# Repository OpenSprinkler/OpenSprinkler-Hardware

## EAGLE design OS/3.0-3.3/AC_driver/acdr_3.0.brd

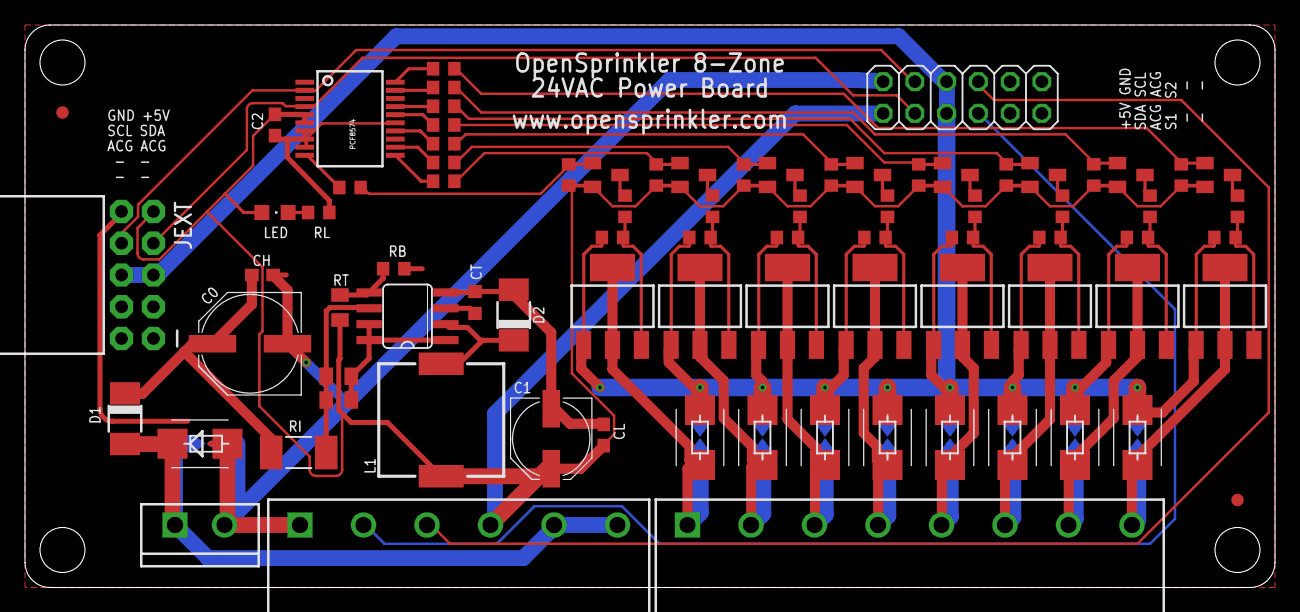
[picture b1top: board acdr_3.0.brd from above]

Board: 2 copper layers, 100.0 x 45.0 mm, 91 parts (0 on the bottom side), 55 nets.

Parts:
C0: 100uF; PANASONIC_E
C1: 100uF; PANASONIC_D
C2: 0.1u; C0603
CH: 0.1u; C0603
CL: 0.1u; C0603
CT: 150pF; C0603K
D1: M7; DO-214AC
D2: SS14; DO-214AC
JCOM: SCREWTERMINAL-5MM-6
JCON: 2X06
JEXT: M05X2RAF; 2X5-RAF
JPWR: SCREWTERMINAL-4MM-2-X
L1: 220uH; SRU1038
LED: CHIPLED_0805
MC3063: 34063; SO08
PCF8574: PCF8574; SSOP20
Q1, Q2, Q3, Q4, Q5, Q6, Q7, Q8: BSS84; SOT23
RB: 1.6K; R0603
RB1, RB2, RB3, RB4, RB5, RB6, RB7, RB8: 470K; R0603
RI: 3.3; R2010
RL: 1K; R0603
RQ1, RQ2, RQ3, RQ4, RQ5, RQ6, RQ7, RQ8: 10K; R0603
RSC, RSC1: 1; R0805
RT: 4.7K; R0805
RT1, RT2, RT3, RT4, RT5, RT6, RT7, RT8: 220; R0603
RU1, RU2, RU3, RU4, RU5, RU6, RU7, RU8: 470K; R0603
S02: SCREWTERMINAL-5MM-8
SP0, SP1, SP2, SP3, SP4, SP5, SP6, SP7, SP8: PCB-SGAP
T1: BT1308W; SOT223
T2, T3, T4, T5, T6, T7, T8: SOT223
TVS0: 43CA; SMB
TVS1: SMBJ48CA; SMB
TVS2, TVS3, TVS4, TVS5, TVS6, TVS7, TVS8: TVSSMB; SMB
U$1, U$2: FIDUCIAL; FIDUCIAL_1MM

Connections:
ACRET: JCON.5, JCON.6, JEXT.5, JEXT.6, RB1.1, RB2.1, RB3.1, RB4.1, RB5.1, RB6.1, RB7.1, RB8.1, SP1.1, SP2.1, SP3.1, SP4.1, SP5.1, SP6.1, SP7.1, SP8.1, T1.1, T2.1, T3.1, T4.1, T5.1, T6.1, T7.1, T8.1, TVS1.C, TVS2.C, TVS3.C, TVS4.C, TVS5.C, TVS6.C, TVS7.C, TVS8.C
COM: D1.A, JCOM.5, JCOM.6, JPWR.1, SP0.1, TVS0.C
GND: C0.-, C1.-, C2.2, CH.2, CL.2, CT.2, D2.A, JCOM.1, JCON.2, JEXT.10, JPWR.2, MC3063.4, PCF8574.7, PCF8574.8, PCF8574.9, PCF8574.15, RB.2, RL.2, SP0.2, TVS0.A
unnamed: MC3063.1, MC3063.7, MC3063.8, RSC.1, RSC1.1
unnamed: Q1.3, RT1.2
unnamed: Q2.3, RT2.2
unnamed: Q3.3, RT3.2
unnamed: Q4.3, RT4.2
unnamed: Q5.3, RT5.2
unnamed: Q6.3, RT6.2
unnamed: RB1.2, RT1.1, T1.3
unnamed: RB2.2, RT2.1, T2.3
unnamed: Q7.3, RT7.2
unnamed: Q8.3, RT8.2
unnamed: Q1.1, RQ1.1, RU1.2
unnamed: Q2.1, RQ2.1, RU2.2
unnamed: Q3.1, RQ3.1, RU3.2
unnamed: RB3.2, RT3.1, T3.3
unnamed: RB4.2, RT4.1, T4.3
unnamed: D2.C, L1.1, MC3063.2
unnamed: RB5.2, RT5.1, T5.3
unnamed: RB6.2, RT6.1, T6.3
unnamed: Q4.1, RQ4.1, RU4.2
unnamed: RB7.2, RT7.1, T7.3
unnamed: RB8.2, RT8.1, T8.3
unnamed: Q5.1, RQ5.1, RU5.2
unnamed: CT.1, MC3063.3
unnamed: Q6.1, RQ6.1, RU6.2
unnamed: MC3063.5, RB.1, RT.2
unnamed: MC3063.6, RI.2, RSC.2, RSC1.2
unnamed: LED.C, RL.1
unnamed: Q7.1, RQ7.1, RU7.2
unnamed: Q8.1, RQ8.1, RU8.2
unnamed: S02.1, SP1.2, T1.2, T1.4, TVS1.A
unnamed: S02.2, SP2.2, T2.2, T2.4, TVS2.A
unnamed: S02.3, SP3.2, T3.2, T3.4, TVS3.A
unnamed: S02.4, SP4.2, T4.2, T4.4, TVS4.A
unnamed: S02.5, SP5.2, T5.2, T5.4, TVS5.A
unnamed: S02.6, SP6.2, T6.2, T6.4, TVS6.A
unnamed: S02.7, SP7.2, T7.2, T7.4, TVS7.A
unnamed: S02.8, SP8.2, T8.2, T8.4, TVS8.A
P0: PCF8574.10, RQ1.2
P1: PCF8574.11, RQ2.2
P2: PCF8574.12, RQ3.2
P3: PCF8574.14, RQ4.2
P4: PCF8574.16, RQ5.2
P5: PCF8574.17, RQ6.2
P6: PCF8574.19, RQ7.2
P7: PCF8574.20, RQ8.2
RECAC: C0.+, CH.1, D1.C, RI.1
S1: JCOM.2, JCON.7
S2: JCOM.3, JCON.8
SCL: JCON.4, JEXT.8, PCF8574.2
SDA: JCON.3, JEXT.7, PCF8574.4
VIN: C1.+, C2.1, CL.1, JCOM.4, JCON.1, JEXT.9, L1.2, LED.A, PCF8574.5, PCF8574.6, Q1.2, Q2.2, Q3.2, Q4.2, Q5.2, Q6.2, Q7.2, Q8.2, RT.1, RU1.1, RU2.1, RU3.1, RU4.1, RU5.1, RU6.1, RU7.1, RU8.1

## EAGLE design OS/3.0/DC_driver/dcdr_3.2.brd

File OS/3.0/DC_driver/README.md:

- Original DC driver board 3.0 uses PCF8574 (8-channel) IO expander with PNP transistor per channel.

- DC driver 3.1 (i.e. revision 1) uses a PCA9555 (16-channel) IO expander.

- DC driver 3.2 (i.e. revision 2) matches master version 3.2 with support for wired Ethernet module.

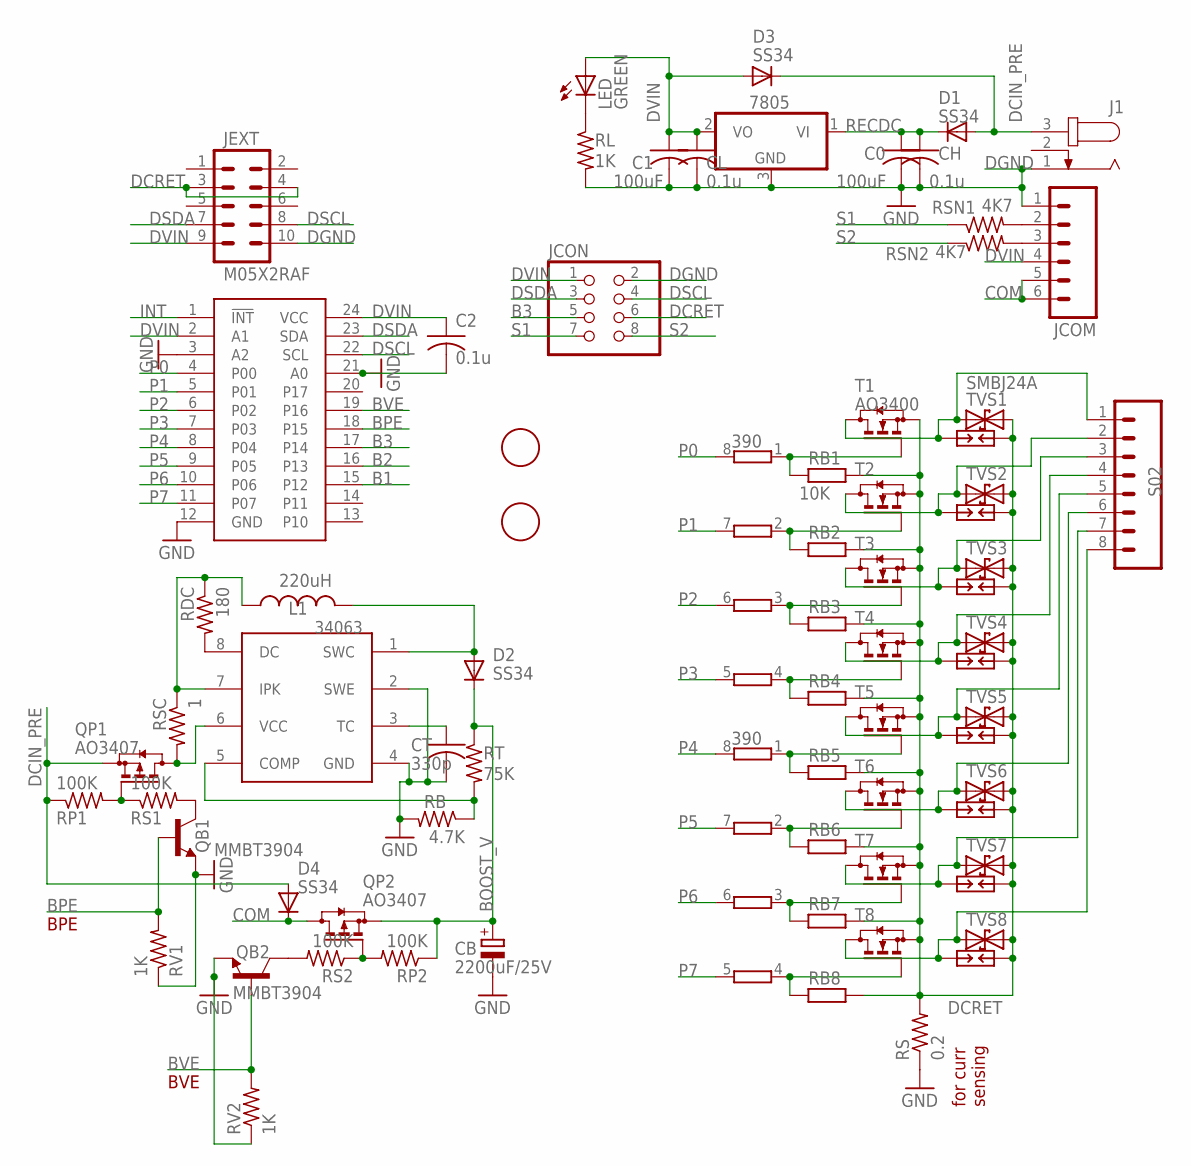
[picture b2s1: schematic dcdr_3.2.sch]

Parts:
7805: 7805DT; TO252
34063: MC34063; SO08
C0, C1: 100uF; C0805K
C2: 0.1u; C0603
CB: 2200uF/25V; E7,5-16
CH: 0.1u; C0603
CL: 0.1u; C0603
CT: 330p; C0603K
D1, D2, D3, D4: SS34; SMB
J1: JACK-PLUG0; SPC4077
JCOM: M065MM; SCREWTERMINAL-5MM-6
JCON: PINHD-2X4; 2X04
JEXT: M05X2RAF; 2X5-RAF
L1: 220uH; CR54
LED: GREEN; CHIPLED_0805
PCA9555: PCA9555; TSSOP24
QB1, QB2: MMBT3904; SOT23-3
QP1, QP2: AO3407; SOT23
RB: 4.7K; R0603
RB1, RB2, RB3, RB4, RB5, RB6, RB7, RB8: 10K; R0603
RDC: 180; R0603
RL: 1K; R0603
RN1, RN2: 390; EXB38V
RP1, RP2: 100K; R0603
RS: 0.2; R2512
RS1, RS2: 100K; R0603
RSC: 1; R0603
RSN1, RSN2: 4K7; R0603
RT: 75K; R0603
RV1, RV2: 1K; R0603
S02: M085MM-8; SCREWTERMINAL-5MM-8
SP1, SP2, SP3, SP4, SP5, SP6, SP7, SP8: PCB-SGAP
T1, T2, T3, T4, T5, T6, T7, T8: AO3400; SOT23
TVS1, TVS2, TVS3, TVS4, TVS5, TVS6, TVS7, TVS8: SMBJ24A; SMB
U$1, U$2: FIDUCIAL; FIDUCIAL_1MM

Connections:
B1: PCA9555.15 (P12)
B2: PCA9555.16 (P13)
B3: JCON.5, PCA9555.17 (P14)
BOOST_V: CB.+, D2.C, QP2.2 (S), RP2.1, RT.1
BPE: PCA9555.18 (P15), QB1.1 (B), RV1.2
BVE: PCA9555.19 (P16), QB2.1 (B), RV2.2
COM: D4.C, JCOM.5, JCOM.6, QP2.3 (D)
DCIN_PRE: D1.A, D3.C, D4.A, J1.3, QP1.2 (S), RP1.1
DCRET: JCON.6, JEXT.3, JEXT.4, RB1.1, RB2.1, RB3.1, RB4.1, RB5.1, RB6.1, RB7.1, RB8.1, RS.2, SP1.1, SP2.1, SP3.1, SP4.1, SP5.1, SP6.1, SP7.1, SP8.1, T1.2 (S), T2.2 (S), T3.2 (S), T4.2 (S), T5.2 (S), T6.2 (S), T7.2 (S), T8.2 (S), TVS1.C, TVS2.C, TVS3.C, TVS4.C, TVS5.C, TVS6.C, TVS7.C, TVS8.C
DGND: 7805.3 (GND), 34063.2 (SWE), 34063.4 (GND), C0.2, C1.2, C2.2, CB.-, CH.2, CL.2, CT.2, J1.1, JCOM.1, JCON.2, JEXT.10, PCA9555.3 (A2), PCA9555.12 (GND), PCA9555.21 (A0), QB1.2 (E), QB2.2 (E), RB.2, RL.2, RS.1, RV1.1, RV2.1
DSCL: JCON.4, JEXT.8, PCA9555.22 (SCL)
DSDA: JCON.3, JEXT.7, PCA9555.23 (SDA)
DVIN: 7805.2 (VO), C1.1, C2.1, CL.1, D3.A, JCOM.4, JCON.1, JEXT.9, LED.A, PCA9555.2 (A1), PCA9555.24 (VCC)
INT: PCA9555.1 (!INT)
unnamed: 34063.1 (SWC), D2.A, L1.P$2 (2)
unnamed: JCOM.2, RSN1.2
unnamed: JCOM.3, RSN2.2
unnamed: RB1.2, RN1.1, T1.1 (G)
unnamed: RB2.2, RN1.2 (1), T2.1 (G)
unnamed: RB3.2, RN1.3 (1), T3.1 (G)
unnamed: RB4.2, RN1.4 (1), T4.1 (G)
unnamed: 34063.3 (TC), CT.1
unnamed: RB5.2, RN2.1, T5.1 (G)
unnamed: RB6.2, RN2.2 (1), T6.1 (G)
unnamed: RB7.2, RN2.3 (1), T7.1 (G)
unnamed: RB8.2, RN2.4 (1), T8.1 (G)
unnamed: 34063.8 (DC), RDC.2
unnamed: 34063.7 (IPK), L1.P$1 (1), RDC.1, RSC.1
unnamed: 34063.6 (VCC), QP1.3 (D), RSC.2
unnamed: LED.C, RL.1
unnamed: 34063.5 (COMP), RB.1, RT.2
unnamed: QP1.1 (G), RP1.2, RS1.1
unnamed: QB2.3 (C), RS2.2
unnamed: QB1.3 (C), RS1.2
unnamed: QP2.1 (G), RP2.2, RS2.1
unnamed: S02.1, SP1.2, T1.3 (D), TVS1.A
unnamed: S02.2, SP2.2, T2.3 (D), TVS2.A
unnamed: S02.3, SP3.2, T3.3 (D), TVS3.A
unnamed: S02.4, SP4.2, T4.3 (D), TVS4.A
unnamed: S02.5, SP5.2, T5.3 (D), TVS5.A
unnamed: S02.6, SP6.2, T6.3 (D), TVS6.A
unnamed: S02.7, SP7.2, T7.3 (D), TVS7.A
unnamed: S02.8, SP8.2, T8.3 (D), TVS8.A
P0: PCA9555.4 (P00), RN1.8 (2)
P1: PCA9555.5 (P01), RN1.7 (2)
P2: PCA9555.6 (P02), RN1.6 (2)
P3: PCA9555.7 (P03), RN1.5 (2)
P4: PCA9555.8 (P04), RN2.8 (2)
P5: PCA9555.9 (P05), RN2.7 (2)
P6: PCA9555.10 (P06), RN2.6 (2)
P7: PCA9555.11 (P07), RN2.5 (2)
RECDC: 7805.1 (VI), C0.1, CH.1, D1.C
S1: JCON.7, RSN1.1
S2: JCON.8, RSN2.1

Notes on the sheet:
BPE
BVE
for curr sensing

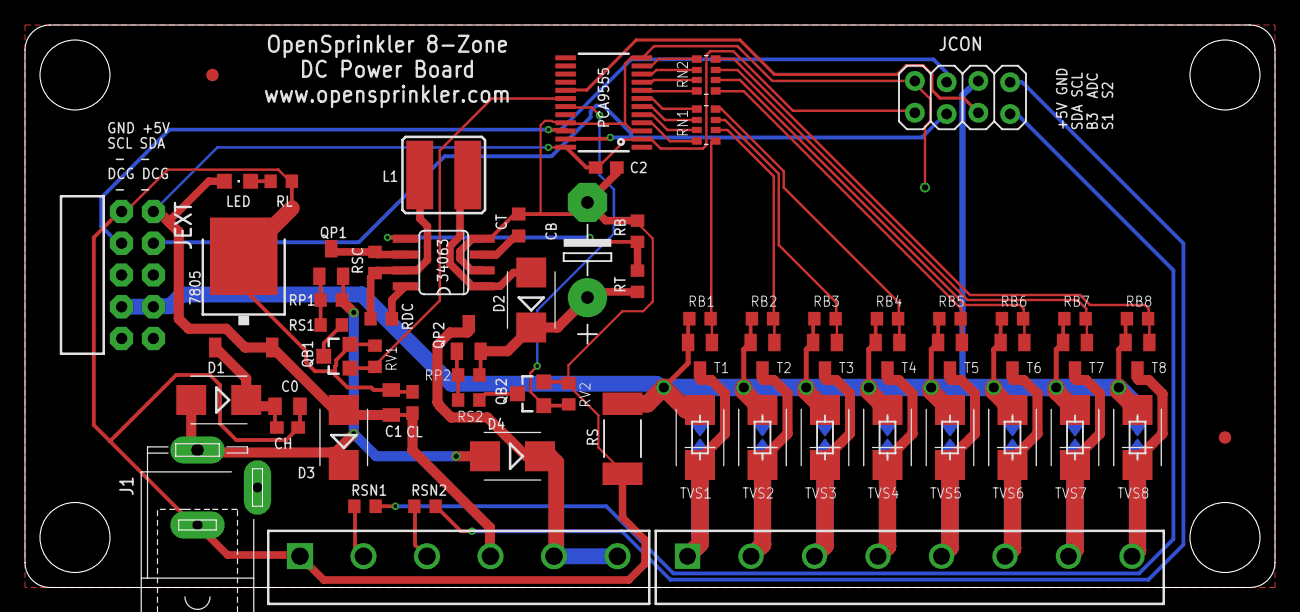
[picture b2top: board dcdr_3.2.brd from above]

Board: 2 copper layers, 100.0 x 45.0 mm, 75 parts (0 on the bottom side), 51 nets.

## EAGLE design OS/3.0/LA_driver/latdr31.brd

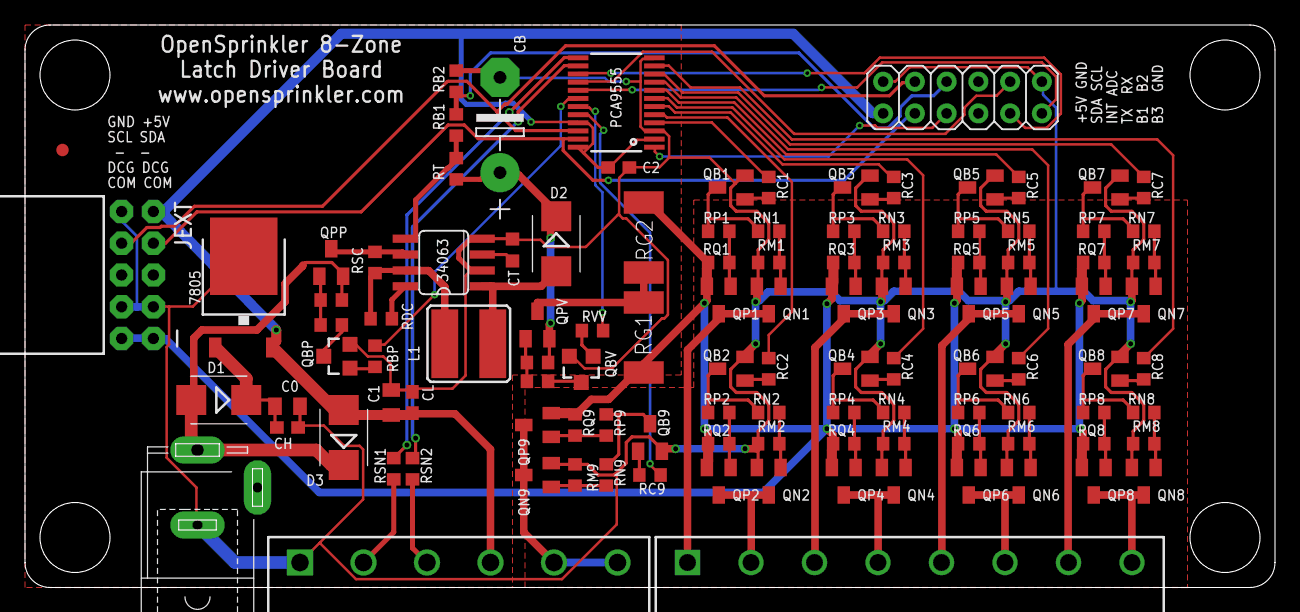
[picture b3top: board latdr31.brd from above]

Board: 2 copper layers, 100.0 x 45.0 mm, 112 parts (0 on the bottom side), 86 nets.

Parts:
0F, 1F: FIDUCIAL; FIDUCIAL_1MM
7805: TO252
34063: SO08
C0, C1: 10uF; C0805K
C2: 0.1u; C0603
CB: 2200uF; E7,5-16
CH: 0.1u; C0603
CL: 0.1u; C0603
CT: 470; C0603K
D1, D2, D3: SS34; SMB
J1: SPC4077
JCOM: SCREWTERMINAL-5MM-6
JCON: 2X06
JEXT: M05X2RAF; 2X5-RAF
L1: 220uH; CR54
PCA9555: PCF8575TSSOP24; TSSOP24
QB1, QB2, QB3, QB4, QB5, QB6, QB7, QB8, QB9: SOT23
QBP: 3904; SOT23-3
QBV: 3904; SOT23-3
QN1, QN2, QN3, QN4, QN5, QN6, QN7, QN8, QN9: 3400; SOT23
QP1, QP2, QP3, QP4, QP5, QP6, QP7, QP8, QP9: 3407; SOT23
QPP: 3407; SOT23
QPV: BSS84; SOT23
RB1: 3.3K; R0603
RB2: 1.5K; R0603
RBP: 1K; R0603
RC1, RC2, RC3, RC4, RC5, RC6, RC7, RC8, RC9: 1K; R0603
RDC: 180; R0603
RG1, RG2: R2512
RM1, RM2, RM3, RM4, RM5, RM6, RM7, RM8, RM9: 470K; R0603
RN1, RN2, RN3, RN4, RN5, RN6, RN7, RN8, RN9: 470K; R0603
RP1, RP2, RP3, RP4, RP5, RP6, RP7, RP8, RP9: 10K; R0603
RPP: 100K; R0603
RPV: 100K; R0603
RQ1, RQ2, RQ3, RQ4, RQ5, RQ6, RQ7, RQ8, RQ9: 10K; R0603
RSC: 1; R0603
RSN1, RSN2: 4K7; R0603
RSP: 100K; R0603
RSV: 100K; R0603
RT: 75K; R0603
RVV: 1K; R0603
S02: SCREWTERMINAL-5MM-8

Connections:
ADC: JCON.6, RB1.2, RB2.1
B1: JCON.9, PCA9555.15
B2: JCON.10, PCA9555.16
B3: JCON.11, PCA9555.17
BOOST_V: CB.+, D2.C, QPV.2, RPV.1, RT.1
BPE: PCA9555.18, RBP.2
BSTV: JEXT.1, JEXT.2, QP1.2, QP2.2, QP3.2, QP4.2, QP5.2, QP6.2, QP7.2, QP8.2, QP9.2, RG1.1, RG2.1, RQ1.1, RQ2.1, RQ3.1, RQ4.1, RQ5.1, RQ6.1, RQ7.1, RQ8.1, RQ9.1
BSTV_PRE: QPV.3, RG1.2, RG2.2
BVC: PCA9555.20, RC9.2
BVE: PCA9555.19, RVV.2
COM: JCOM.5, JCOM.6, QN9.3, QP9.3
DCIN_PRE: D1.A, D3.C, J1.3, QPP.2, RPP.1
DSCL: JCON.4, JEXT.8, PCA9555.22
DSDA: JCON.3, JEXT.7, PCA9555.23
DVIN: 7805.2, C1.1, C2.1, CL.1, D3.A, JCOM.4, JCON.1, JEXT.9, PCA9555.2, PCA9555.21, PCA9555.24
GND: 7805.3, 34063.2, 34063.4, C0.2, C1.2, C2.2, CB.-, CH.2, CL.2, CT.2, J1.1, JCOM.1, JCON.2, JCON.12, JEXT.3, JEXT.4, JEXT.10, PCA9555.3, PCA9555.12, QB1.2, QB2.2, QB3.2, QB4.2, QB5.2, QB6.2, QB7.2, QB8.2, QB9.2, QBP.2, QBV.2, QN1.2, QN2.2, QN3.2, QN4.2, QN5.2, QN6.2, QN7.2, QN8.2, QN9.2, RB2.2, RN1.2, RN2.2, RN3.2, RN4.2, RN5.2, RN6.2, RN7.2, RN8.2, RN9.2
INT: JCON.5, PCA9555.1
unnamed: 34063.1, D2.A, L1.P$2
unnamed: JCOM.2, RSN1.2
unnamed: JCOM.3, RSN2.2
unnamed: QB2.1, RC2.1
unnamed: QB9.1, RC9.1
unnamed: QB1.1, RC1.1
unnamed: QB4.1, RC4.1
unnamed: QB3.1, RC3.1
unnamed: 34063.3, CT.1
unnamed: QB5.1, RC5.1
unnamed: QB6.1, RC6.1
unnamed: 34063.8, RDC.2
unnamed: 34063.7, L1.P$1, RDC.1, RSC.1
unnamed: 34063.6, QPP.3, RSC.2
unnamed: QBP.1, RBP.1
unnamed: 34063.5, RB1.1, RT.2
unnamed: QPP.1, RPP.2, RSP.1
unnamed: QB7.1, RC7.1
unnamed: QBV.3, RSV.2
unnamed: QBP.3, RSP.2
unnamed: QPV.1, RPV.2, RSV.1
unnamed: QB8.1, RC8.1
unnamed: QBV.1, RVV.1
unnamed: QB9.3, RM9.2, RP9.1
unnamed: QB1.3, RM1.2, RP1.1
unnamed: QB2.3, RM2.2, RP2.1
unnamed: QB3.3, RM3.2, RP3.1
unnamed: QB4.3, RM4.2, RP4.1
unnamed: QB5.3, RM5.2, RP5.1
unnamed: QB6.3, RM6.2, RP6.1
unnamed: QB7.3, RM7.2, RP7.1
unnamed: QB8.3, RM8.2, RP8.1
unnamed: QP9.1, RP9.2, RQ9.2
unnamed: QP1.1, RP1.2, RQ1.2
unnamed: QP2.1, RP2.2, RQ2.2
unnamed: QP3.1, RP3.2, RQ3.2
unnamed: QP4.1, RP4.2, RQ4.2
unnamed: QP5.1, RP5.2, RQ5.2
unnamed: QP6.1, RP6.2, RQ6.2
unnamed: QP7.1, RP7.2, RQ7.2
unnamed: QP8.1, RP8.2, RQ8.2
unnamed: QN9.1, RM9.1, RN9.1
unnamed: QN1.1, RM1.1, RN1.1
unnamed: QN2.1, RM2.1, RN2.1
unnamed: QN3.1, RM3.1, RN3.1
unnamed: QN4.1, RM4.1, RN4.1
unnamed: QN5.1, RM5.1, RN5.1
unnamed: QN6.1, RM6.1, RN6.1
unnamed: QN7.1, RM7.1, RN7.1
unnamed: QN8.1, RM8.1, RN8.1
P0: PCA9555.4, RC1.2
P1: PCA9555.5, RC2.2
P2: PCA9555.6, RC3.2
P3: PCA9555.7, RC4.2
P4: PCA9555.8, RC5.2
P5: PCA9555.9, RC6.2
P6: PCA9555.10, RC7.2
P7: PCA9555.11, RC8.2
RECDC: 7805.1, C0.1, CH.1, D1.C
S1: PCA9555.13, RSN1.1
S2: PCA9555.14, RSN2.1
T01: QN1.3, QP1.3, S02.1
T02: QN2.3, QP2.3, S02.2
T03: QN3.3, QP3.3, S02.3
T04: QN4.3, QP4.3, S02.4
T05: QN5.3, QP5.3, S02.5
T06: QN6.3, QP6.3, S02.6
T07: QN7.3, QP7.3, S02.7
T08: QN8.3, QP8.3, S02.8

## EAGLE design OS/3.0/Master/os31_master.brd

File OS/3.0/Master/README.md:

- Original OS 3.0 design uses a PCF8574 (8-channel) IO expander on the main controller and a separate PCF8574 on the driver board.

- OS 3.1 (i.e. revision 1) improved the design by combining the two into a single PCA9555 (16-channel) IO expander. It has also moved the current sensing circuitry to the driver board, to avoid routing it onto the main controller board.

- OS 3.2 (i.e. revision 2) supports wired Ethernet module by adding a 2x5 connector to be linked to a ENC28J60 module, and it changed GPIO pin assignments in order to free up SPI pins for the Ethernet module.

- OS 3.3 (i.e. revision 3) supports W5500 wired Ethernet module, which provides better reliability than ENC28J60. It's design is largely the same with OS 3.2 but the ethernet module pins have been changed to match that of W5500.

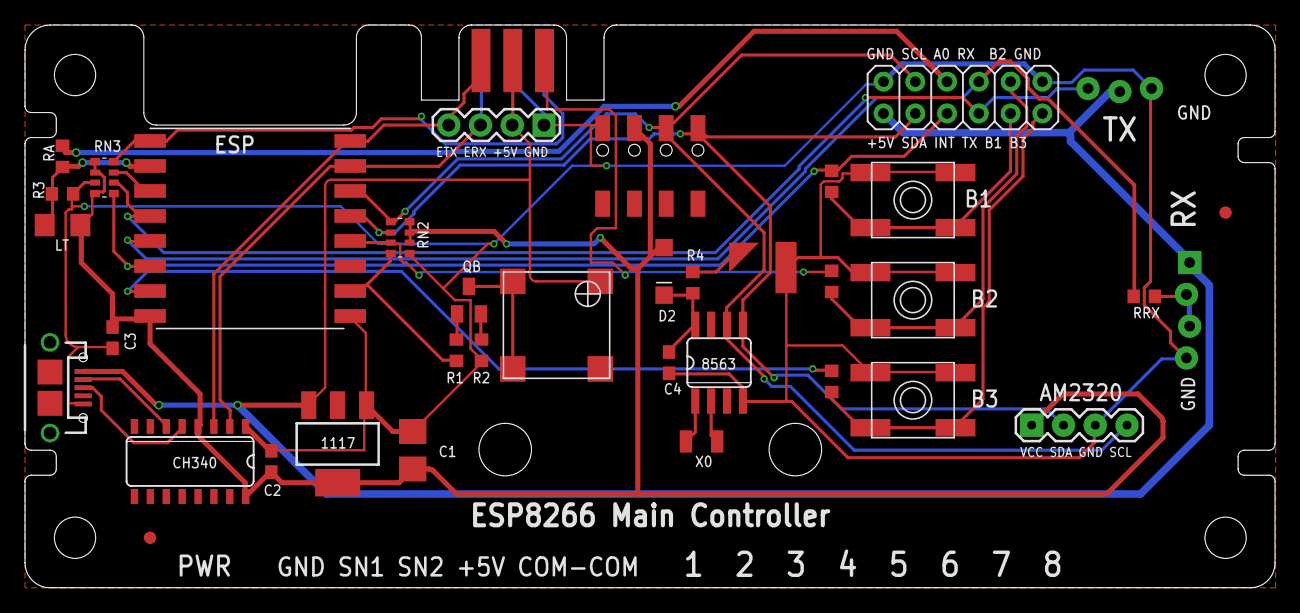
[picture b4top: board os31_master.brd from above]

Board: 2 copper layers, 100.0 x 45.0 mm, 38 parts (0 on the bottom side), 30 nets.

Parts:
1F, 2F: FIDUCIAL; FIDUCIAL_1MM
1117: BL1117-33; SOT223
8563: PCF8563; SO08
AM2320: 1X04-NARROW
B1, B2, B3: SPST_TACTEVQQ2; EVQ-Q2
BAT: XH414; BATTCON_XH414
BUZ: BUZZER; SMT-8585-BUZZER
C1: 100uF; CT3528
C2, C3, C4: 0.1u; C0603
CH340: CH340C; SO16
D2: LL4148; SOD123
ESP: ESP-12N; ESP12_WES
JP1: M04X2; 2X06
JP2: 1X04
LCD: SSD1306_OLED_I2CSMD3; SSD1306_OLED_I2C_SMD3
LT: 100K; R1206
QB: MMBT3904; SOT23
R1: 1K; R0603
R2: 10; R0603
R3, R4: 10K; R0603
RA: 1; R0603
RB1, RB2, RB3: 1; R0603
RN2: 1Kx4; EXB38V
RN3: 10Kx4; EXB38V
RRX: 1K; R0603
RX: 1X04_LOCK
TX: 1X03_LOCK
U$3: GOLDFINGER_2X3
USB: USBMICROB2; USB-MICROB2
X0: 32.768kHz; MM20SS1

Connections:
ADC: ESP.ADC, LT.1, R3.1, RA.2
B1: B1.1, B1.2, JP1.9, RB1.1
B2: B2.1, B2.2, JP1.10, RB2.1
B3: B3.1, B3.2, JP1.11, RB3.1
D+: CH340.5, USB.D+
D-: CH340.6, USB.D-
EN: ESP.EN, RN3.7
ERX: CH340.2, ESP.RX, JP2.3, U$3.4
ETX: CH340.3, ESP.TX, JP2.4, U$3.1
GND: 1117.1, 8563.4, AM2320.3, B1.3, B1.4, B2.3, B2.4, B3.3, B3.4, BAT.P$1, C1.+, C2.1, C3.2, C4.2, CH340.1, ESP.GND, JP1.2, JP1.12, JP2.1, LCD.1, R2.1, R3.2, RN2.5, RN3.3, RX.4, TX.3, U$3.5, USB.GND
GPIO0: ESP.0, RB2.2, RN2.3, U$3.3
GPIO12: ESP.12, JP1.5, RB1.2, RN3.5
GPIO13: ESP.13, RB3.2
GPIO14: ESP.14, JP1.8, RRX.2
GPIO15: ESP.15, R1.1, RN2.4
GPIO16: ESP.16, JP1.7, RN3.6, TX.1
unnamed: 8563.1, X0.1
unnamed: BUZ.-, BUZ.A-, QB.3
unnamed: QB.1, R1.2
unnamed: QB.2, R2.2
unnamed: JP1.6, RA.1
unnamed: 8563.8, C4.1, D2.C, R4.2
unnamed: RRX.1, RX.2, RX.3
unnamed: 8563.2, X0.4
unnamed: BAT.P$2, R4.1
RST: ESP.RST, RN3.8, U$3.6
SCL: 8563.6, AM2320.4, ESP.4, JP1.4, LCD.3, RN2.1
SDA: 8563.5, AM2320.2, ESP.5, JP1.3, LCD.4, RN2.2
VCC: 1117.4, AM2320.1, C1.-, C2.2, C3.1, CH340.4, CH340.16, D2.A, ESP.VCC, LCD.2, LT.2, RN2.6, RN2.7, RN2.8, RN3.1, RN3.2, RN3.4
VIN: 1117.3, BUZ.+, JP1.1, JP2.2, RX.1, TX.2, U$3.2, USB.VBUS

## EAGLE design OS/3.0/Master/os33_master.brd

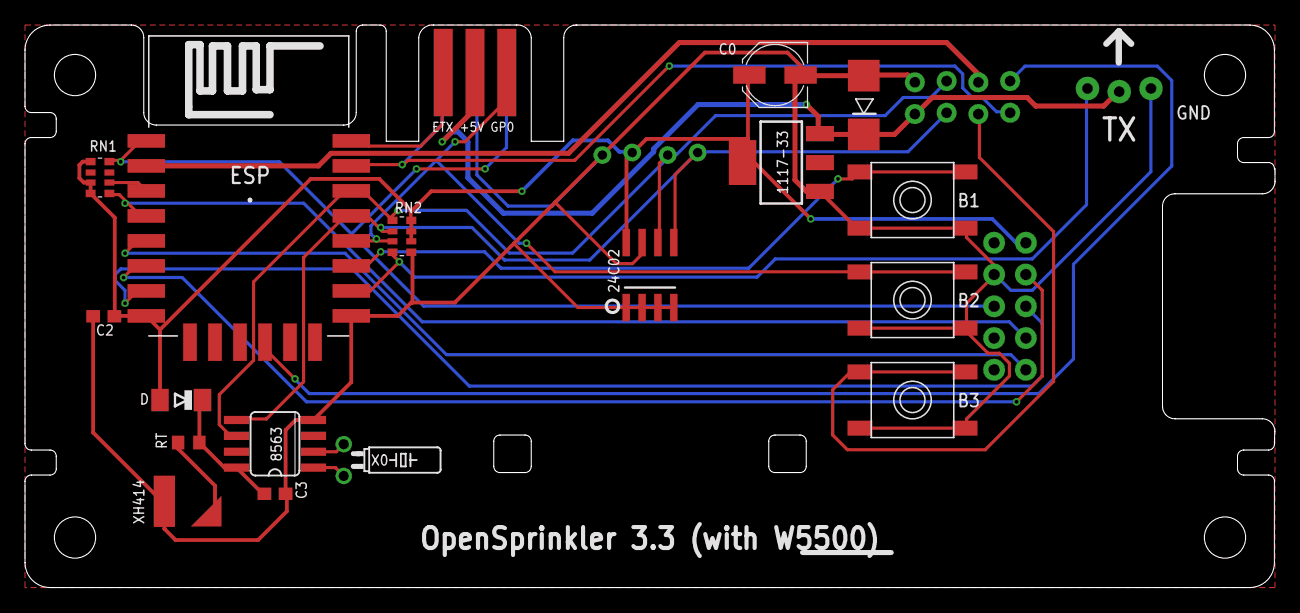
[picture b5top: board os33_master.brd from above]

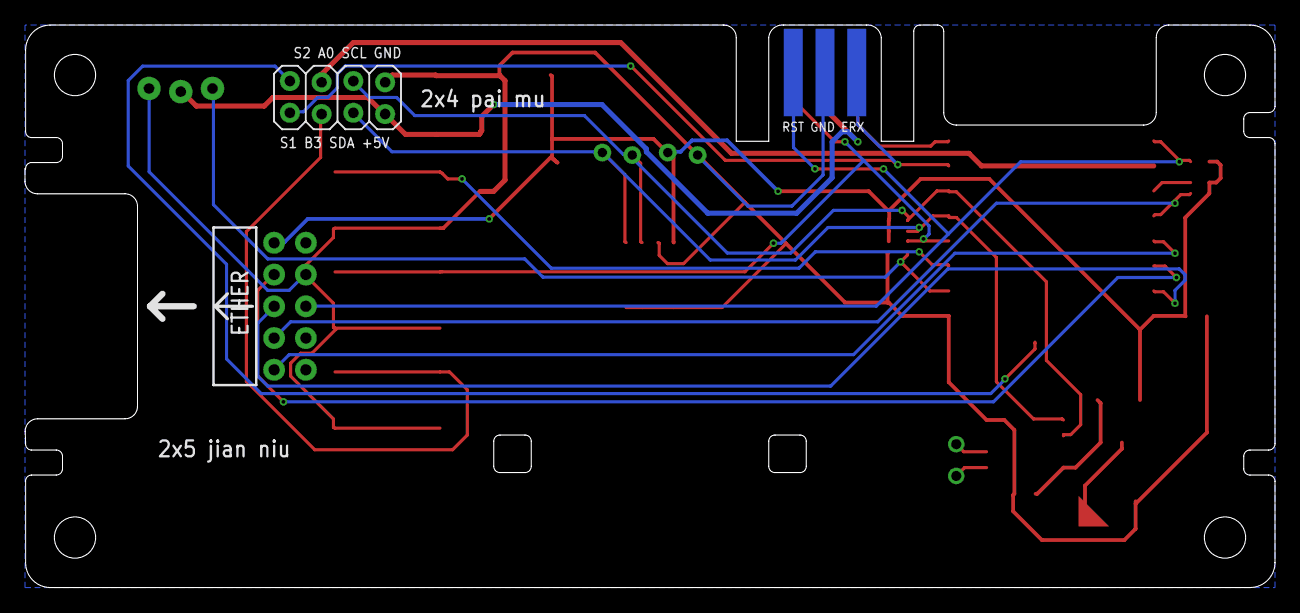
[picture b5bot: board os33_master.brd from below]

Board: 2 copper layers, 100.0 x 45.0 mm, 22 parts (2 on the bottom side), 23 nets.

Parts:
24C02: 24C02CSN; SO-08
1117-33: BL1117-33; SOT223
8563: PCF8563; SO08
B1, B2, B3: SPST_TACTEVQQ2; EVQ-Q2
C0: PANASONIC_C
C2, C3: 0.1u; C0603
D: LL4148; MINIMELF
ESP: ESP8266; ESP12E-SMD
ETHER: M05X2RAF; 2X5-RAF
JP1: M04X2; 2X04
LCD: SSD1306_OLED_I2CPCB0.75BB; SSD1306_OLED_I2C_PCB_0.75BB
RN1: 10Kx4; EXB38V
RN2: 1Kx4; EXB38V
RT: 10K; R0603
TVS: SMAJ5.6A; SMADIODE
TX: 1X03_LOCK
U$3: GOLDFINGER_2X3
X0: 32.768kHz; TC26H
XH414: XH414; BATTCON_XH414

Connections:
ADC: ESP.ADC, JP1.4
B3: B3.1, B3.2, JP1.3
EN: ESP.CH_PD, RN1.6
ERX: ESP.RXD0, JP1.1, U$3.4
ETX: ESP.TXD0, U$3.1
GND: 24C02.1, 24C02.2, 24C02.3, 24C02.4, 24C02.7, 1117-33.1, 8563.4, B1.3, B1.4, B2.3, B2.4, B3.3, B3.4, C0.-, C2.2, C3.2, ESP.GND, ETHER.7, JP1.8, LCD.1, RN2.5, TVS.A, TX.3, U$3.5, XH414.P$1
GPIO0: B2.1, B2.2, ESP.GPIO0, RN2.3, U$3.3
GPIO2: B1.1, B1.2, ESP.GPIO2
GPIO10: ESP.GPIO10, JP1.2
GPIO15: ESP.GPIO15, RN2.4, TX.1
GPIO16: ESP.GPIO16, ETHER.4, RN1.5
MISO: ESP.GPIO12, ETHER.8
MOSI: ESP.GPIO13, ETHER.6
unnamed: 8563.1, X0.2
unnamed: 8563.2, X0.1
unnamed: 8563.8, C3.1, D.C, RT.2
unnamed: RT.1, XH414.P$2
RST: ESP.RESET, ETHER.5, RN1.8, U$3.6
SCK: ESP.GPIO14, ETHER.2
SCL: 24C02.6, 8563.6, ESP.GPIO5, JP1.6, LCD.3, RN2.1
SDA: 24C02.5, 8563.5, ESP.GPIO4, JP1.5, LCD.4, RN2.2
VCC: 24C02.8, 1117-33.4, C0.+, C2.1, D.A, ESP.VCC, ETHER.10, LCD.2, RN1.1, RN1.3, RN1.4, RN2.6, RN2.7, RN2.8
VIN: 1117-33.3, JP1.7, TVS.C, TX.2, U$3.2

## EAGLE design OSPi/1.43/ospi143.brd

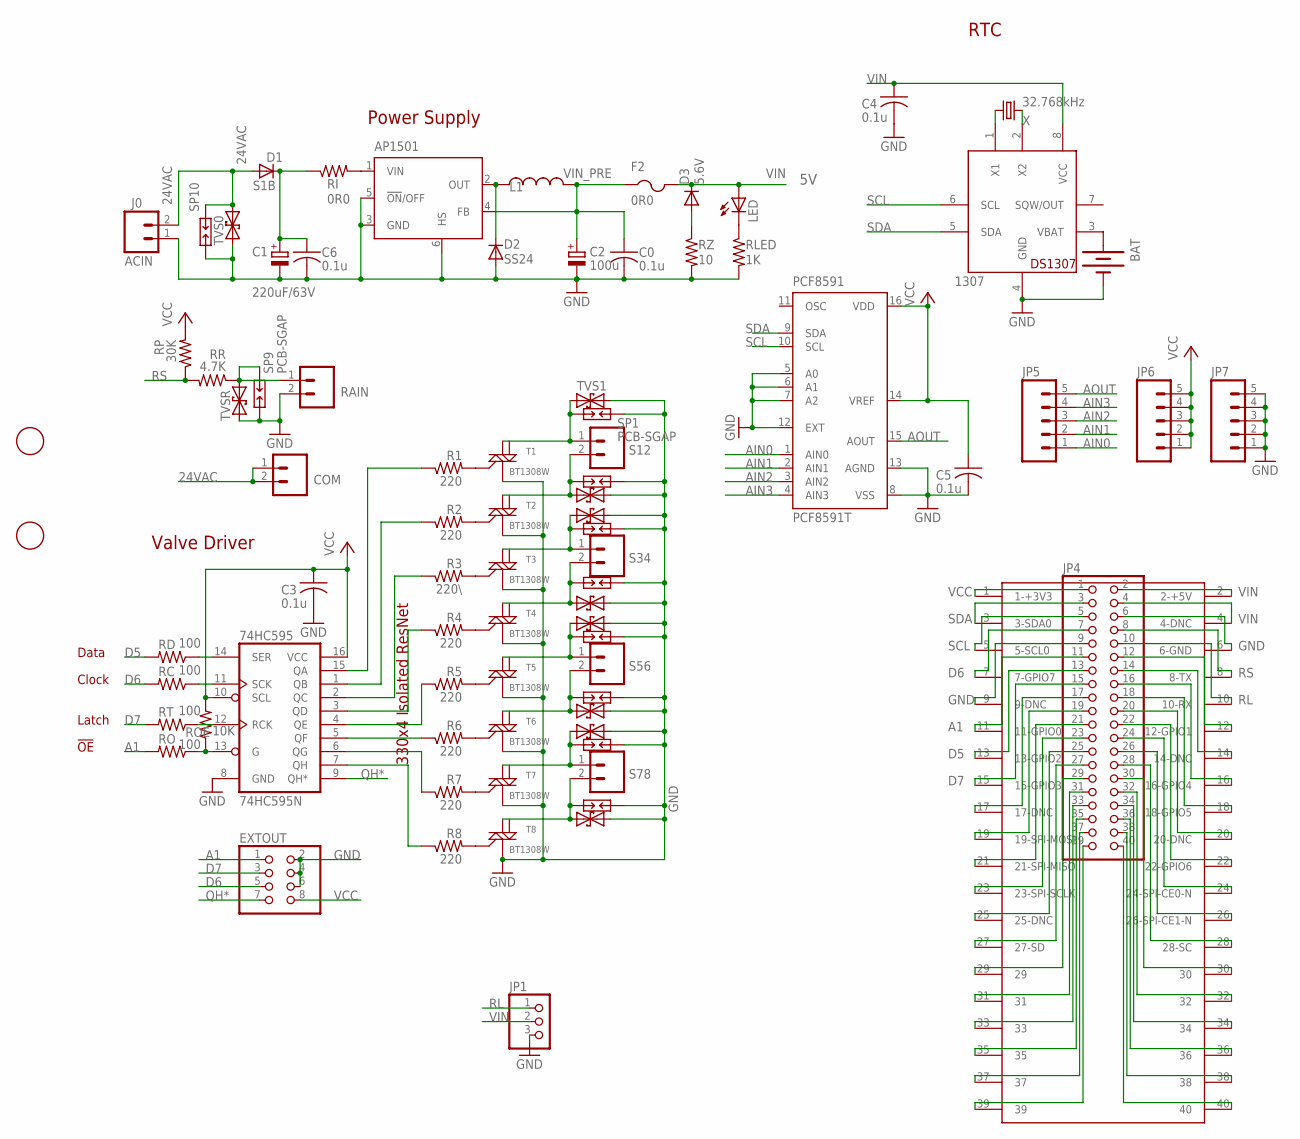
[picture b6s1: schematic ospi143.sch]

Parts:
74HC595: 74HC595N; SO16
1307: DS1307; SO08
AP1501: LM2596S; TO263-5
BAT: BATTERYBATTERY_12MM_SMT; BATTCON_12MM_SMT
C0, C3, C4, C5, C6: 0.1u; C0603K
C1: 220uF/63V; PANASONIC_E
C2: 100u; PANASONIC_E
COM: M025MM-X; SCREWTERMINAL-5MM-2-X
D1: S1B; DO-214AC
D2: SS24; SMB
D3: 5.6V; MINIMELF
EXTOUT: PINHD-2X4/90; 2X04/90
F2: 0R0; 1812
J0: ACIN; SCREWTERMINAL-4MM-2-X
JP1: PINHD-1X3; 1X03
JP4: PINHD-2X20; 2X20
JP5, JP6, JP7: M05PTH; 1X05
L1: 150uH; CDRH125
LED: LEDCHIPLED_0805; CHIPLED_0805
PCF8591: PCF8591T; SO16W
R1, R2, R4, R5, R6, R7, R8: 220; R0603
R3: 220\; R0603
RAIN: M025MM-X; SCREWTERMINAL-5MM-2-X
RC: 100; R0603
RD: 100; R0603
RI: 0R0; R2010
RLED: 1K; R0805
RO: 100; R0603
ROE: 10K; R0603
RP: 30K; R0805
RR: 4.7K; R0805
RT: 100; R0603
RZ: 10; R2010
S12, S34, S56, S78: M025MM-X; SCREWTERMINAL-5MM-2-X
SP1, SP2, SP3, SP4, SP5, SP6, SP7, SP8, SP9, SP10: PCB-SGAP
T1, T2, T3, T4, T5, T6, T7, T8: BT1308W; SOT223
TVS0, TVS1, TVS2, TVS3, TVS4, TVS5, TVS6, TVS7, TVS8: TVSSMB; SMB
TVSR: TVSSMB; SMB
U$1, U$3: FIDUCIAL; FIDUCIAL_1MM
U$2: RPIB+
X: 32.768kHz; MM20SS

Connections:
24VAC: COM.1, COM.2, D1.A, J0.2, SP10.1, TVS0.C
A1: EXTOUT.1, JP4.11, RO.2, U$2.11 (11-GPIO0)
AIN0: JP5.1, PCF8591.1 (AIN0)
AIN1: JP5.2, PCF8591.2 (AIN1)
AIN2: JP5.3, PCF8591.3 (AIN2)
AIN3: JP5.4, PCF8591.4 (AIN3)
AOUT: JP5.5, PCF8591.15 (AOUT)
D5: JP4.13, RD.2, U$2.13 (13-GPIO2)
D6: EXTOUT.5, JP4.7, RC.2, U$2.7 (7-GPIO7)
D7: EXTOUT.3, JP4.15, RT.2, U$2.15 (15-GPIO3)
GND: 74HC595.8 (GND), 1307.4 (GND), AP1501.3 (GND), AP1501.5 (!ON!/OFF), AP1501.6 (HS), BAT.P$1 (-), C0.2, C1.-, C2.-, C3.2, C4.2, C5.2, C6.2, D2.A, EXTOUT.2, EXTOUT.4, EXTOUT.6, J0.1, JP1.3, JP4.6, JP4.9, JP7.1, JP7.2, JP7.3, JP7.4, JP7.5, PCF8591.5 (A0), PCF8591.6 (A1), PCF8591.7 (A2), PCF8591.8 (VSS), PCF8591.12 (EXT), PCF8591.13 (AGND), RAIN.2, RLED.2, RZ.2, SP1.1, SP2.1, SP3.1, SP4.1, SP5.1, SP6.1, SP7.1, SP8.1, SP9.2, SP10.2, T1.1 (M1), T2.1 (M1), T3.1 (M1), T4.1 (M1), T5.1 (M1), T6.1 (M1), T7.1 (M1), T8.1 (M1), TVS0.A, TVS1.C, TVS2.C, TVS3.C, TVS4.C, TVS5.C, TVS6.C, TVS7.C, TVS8.C, TVSR.A, U$2.6 (6-GND), U$2.9 (9-DNC)
unnamed: LED.C, RLED.1
unnamed: C1.+, C6.1, D1.C, RI.1
unnamed: R1.2, T1.3 (G)
unnamed: 74HC595.5 (QF), R6.1
unnamed: 74HC595.6 (QG), R7.1
unnamed: D3.A, RZ.1
unnamed: 74HC595.7 (QH), R8.1
unnamed: AP1501.2 (OUT), D2.C, L1.1
unnamed: 1307.2 (X2), X.4 (2)
unnamed: 74HC595.4 (QE), R5.1
unnamed: 74HC595.3 (QD), R4.1
unnamed: 74HC595.2 (QC), R3.1
unnamed: 74HC595.1 (QB), R2.1
unnamed: 74HC595.15 (QA), R1.1
unnamed: R2.2, T2.3 (G)
unnamed: S12.1, SP1.2, T1.2 (M2), TVS1.A
unnamed: S12.2, SP2.2, T2.2 (M2), TVS2.A
unnamed: S34.1, SP3.2, T3.2 (M2), TVS3.A
unnamed: R3.2, T3.3 (G)
unnamed: S34.2, SP4.2, T4.2 (M2), TVS4.A
unnamed: R4.2, T4.3 (G)
unnamed: S56.1, SP5.2, T5.2 (M2), TVS5.A
unnamed: S56.2, SP6.2, T6.2 (M2), TVS6.A
unnamed: S78.1, SP7.2, T7.2 (M2), TVS7.A
unnamed: S78.2, SP8.2, T8.2 (M2), TVS8.A
unnamed: R5.2, T5.3 (G)
unnamed: R6.2, T6.3 (G)
unnamed: R7.2, T7.3 (G)
unnamed: R8.2, T8.3 (G)
unnamed: 1307.1 (X1), X.1
unnamed: RAIN.1, RR.1, SP9.1, TVSR.C
unnamed: 74HC595.14 (SER), RD.1
unnamed: 74HC595.11 (SCK), RC.1
unnamed: 74HC595.12 (RCK), RT.1
unnamed: 1307.3 (VBAT), BAT.P$2 (+)
unnamed: JP4.12, U$2.12 (12-GPIO1)
unnamed: JP4.14, U$2.14 (14-DNC)
unnamed: JP4.16, U$2.16 (16-GPIO4)
unnamed: 74HC595.13 (G), RO.1, ROE.1
unnamed: JP4.23, U$2.23 (23-SPI-SCLK)
unnamed: JP4.25, U$2.25 (25-DNC)
unnamed: JP4.27, U$2.27 (27-SD)
unnamed: JP4.29, U$2.29
unnamed: JP4.39, U$2.39
unnamed: JP4.37, U$2.37
unnamed: JP4.17, U$2.17 (17-DNC)
unnamed: JP4.19, U$2.19 (19-SPI-MOSI)
unnamed: JP4.21, U$2.21 (21-SPI-MISO)
unnamed: JP4.35, U$2.35
unnamed: JP4.33, U$2.33
unnamed: JP4.31, U$2.31
unnamed: JP4.34, U$2.34
unnamed: JP4.36, U$2.36
unnamed: JP4.38, U$2.38
unnamed: JP4.40, U$2.40
unnamed: AP1501.1 (VIN), RI.2
unnamed: JP4.18, U$2.18 (18-GPIO5)
unnamed: JP4.20, U$2.20 (20-DNC)
unnamed: JP4.22, U$2.22 (22-GPIO6)
unnamed: JP4.24, U$2.24 (24-SPI-CE0-N)
unnamed: JP4.26, U$2.26 (26-SPI-CE1-N)
unnamed: JP4.28, U$2.28 (28-SC)
unnamed: JP4.30, U$2.30
unnamed: JP4.32, U$2.32
QH*: 74HC595.9 (QH*), EXTOUT.7
RL: JP1.1, JP4.10, U$2.10 (10-RX)
RS: JP4.8, RP.1, RR.2, U$2.8 (8-TX)
SCL: 1307.6 (SCL), JP4.5, PCF8591.10 (SCL), U$2.5 (5-SCL0)
SDA: 1307.5 (SDA), JP4.3, PCF8591.9 (SDA), U$2.3 (3-SDA0)
VCC: 74HC595.10 (SCL), 74HC595.16 (VCC), C3.1, C5.1, EXTOUT.8, JP4.1, JP6.1, JP6.2, JP6.3, JP6.4, JP6.5, PCF8591.14 (VREF), PCF8591.16 (VDD), ROE.2, RP.2, U$2.1 (1-+3V3)
VIN: 1307.8 (VCC), C4.1, D3.C, F2.2, JP1.2, JP4.2, JP4.4, LED.A, U$2.2 (2-+5V), U$2.4 (4-DNC)
VIN_PRE: AP1501.4 (FB), C0.1, C2.+, F2.1, L1.2

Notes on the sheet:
Power Supply
Valve Driver
Data
Clock
Latch
330x4 Isolated ResNet
!OE
RTC

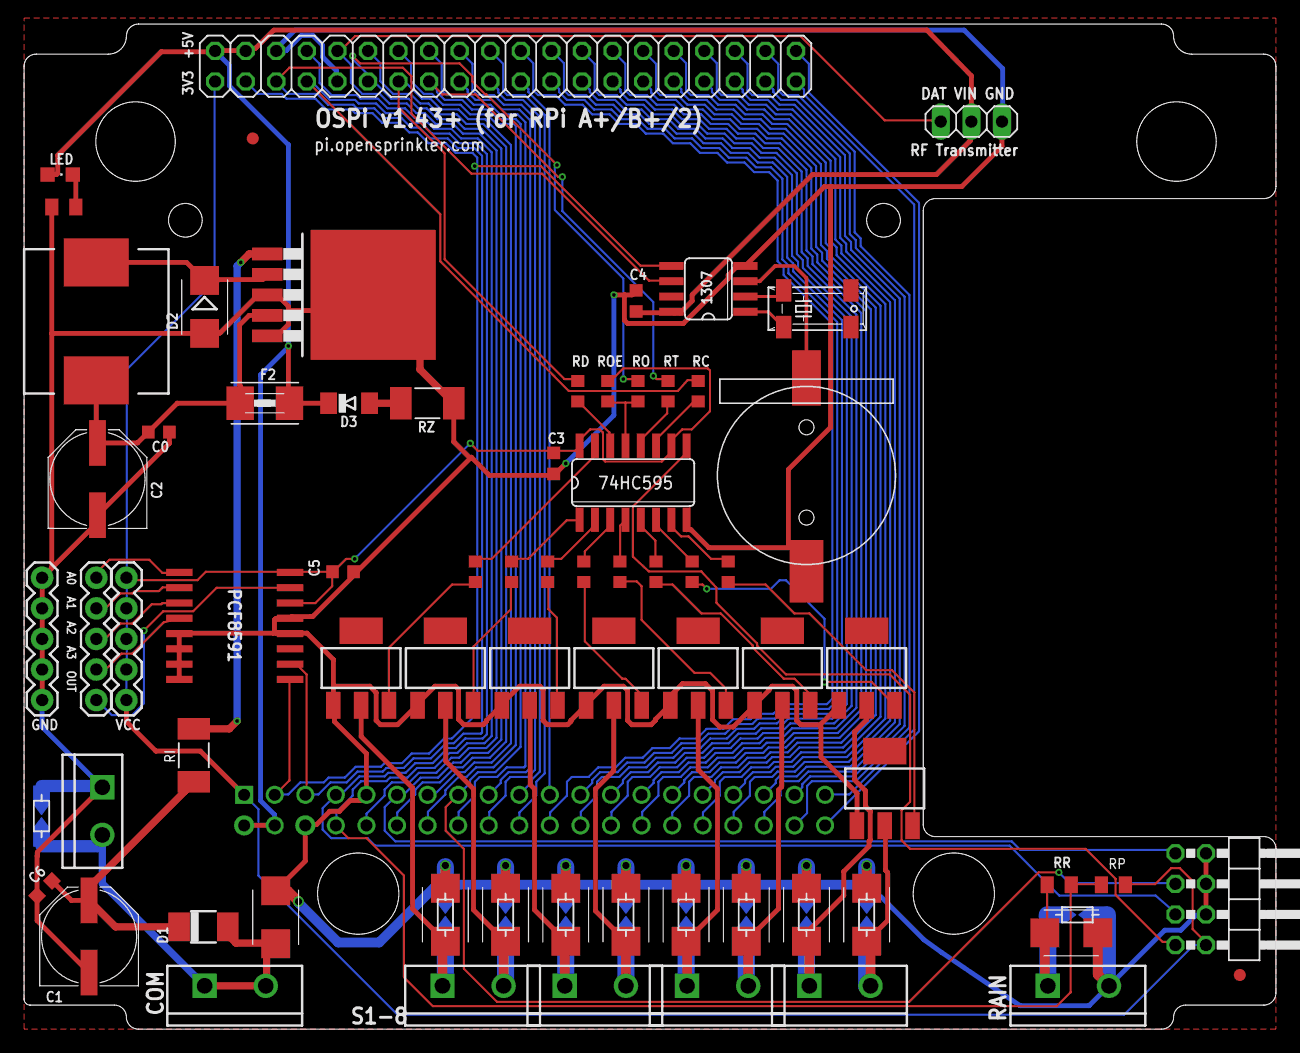
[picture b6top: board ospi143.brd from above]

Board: 2 copper layers, 104.0 x 83.5 mm, 81 parts (1 on the bottom side), 83 nets.

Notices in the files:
parts and their libraries:
SparkFunNew: Licensing: CC v3.0 Share-Alike You are welcome to use this library for commercial purposes.
